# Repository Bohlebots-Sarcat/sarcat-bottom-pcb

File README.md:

# main/sarcat-bottom-pcb

## Sarcat PCB
___
Bohlebots Sarcat bottom circuit board

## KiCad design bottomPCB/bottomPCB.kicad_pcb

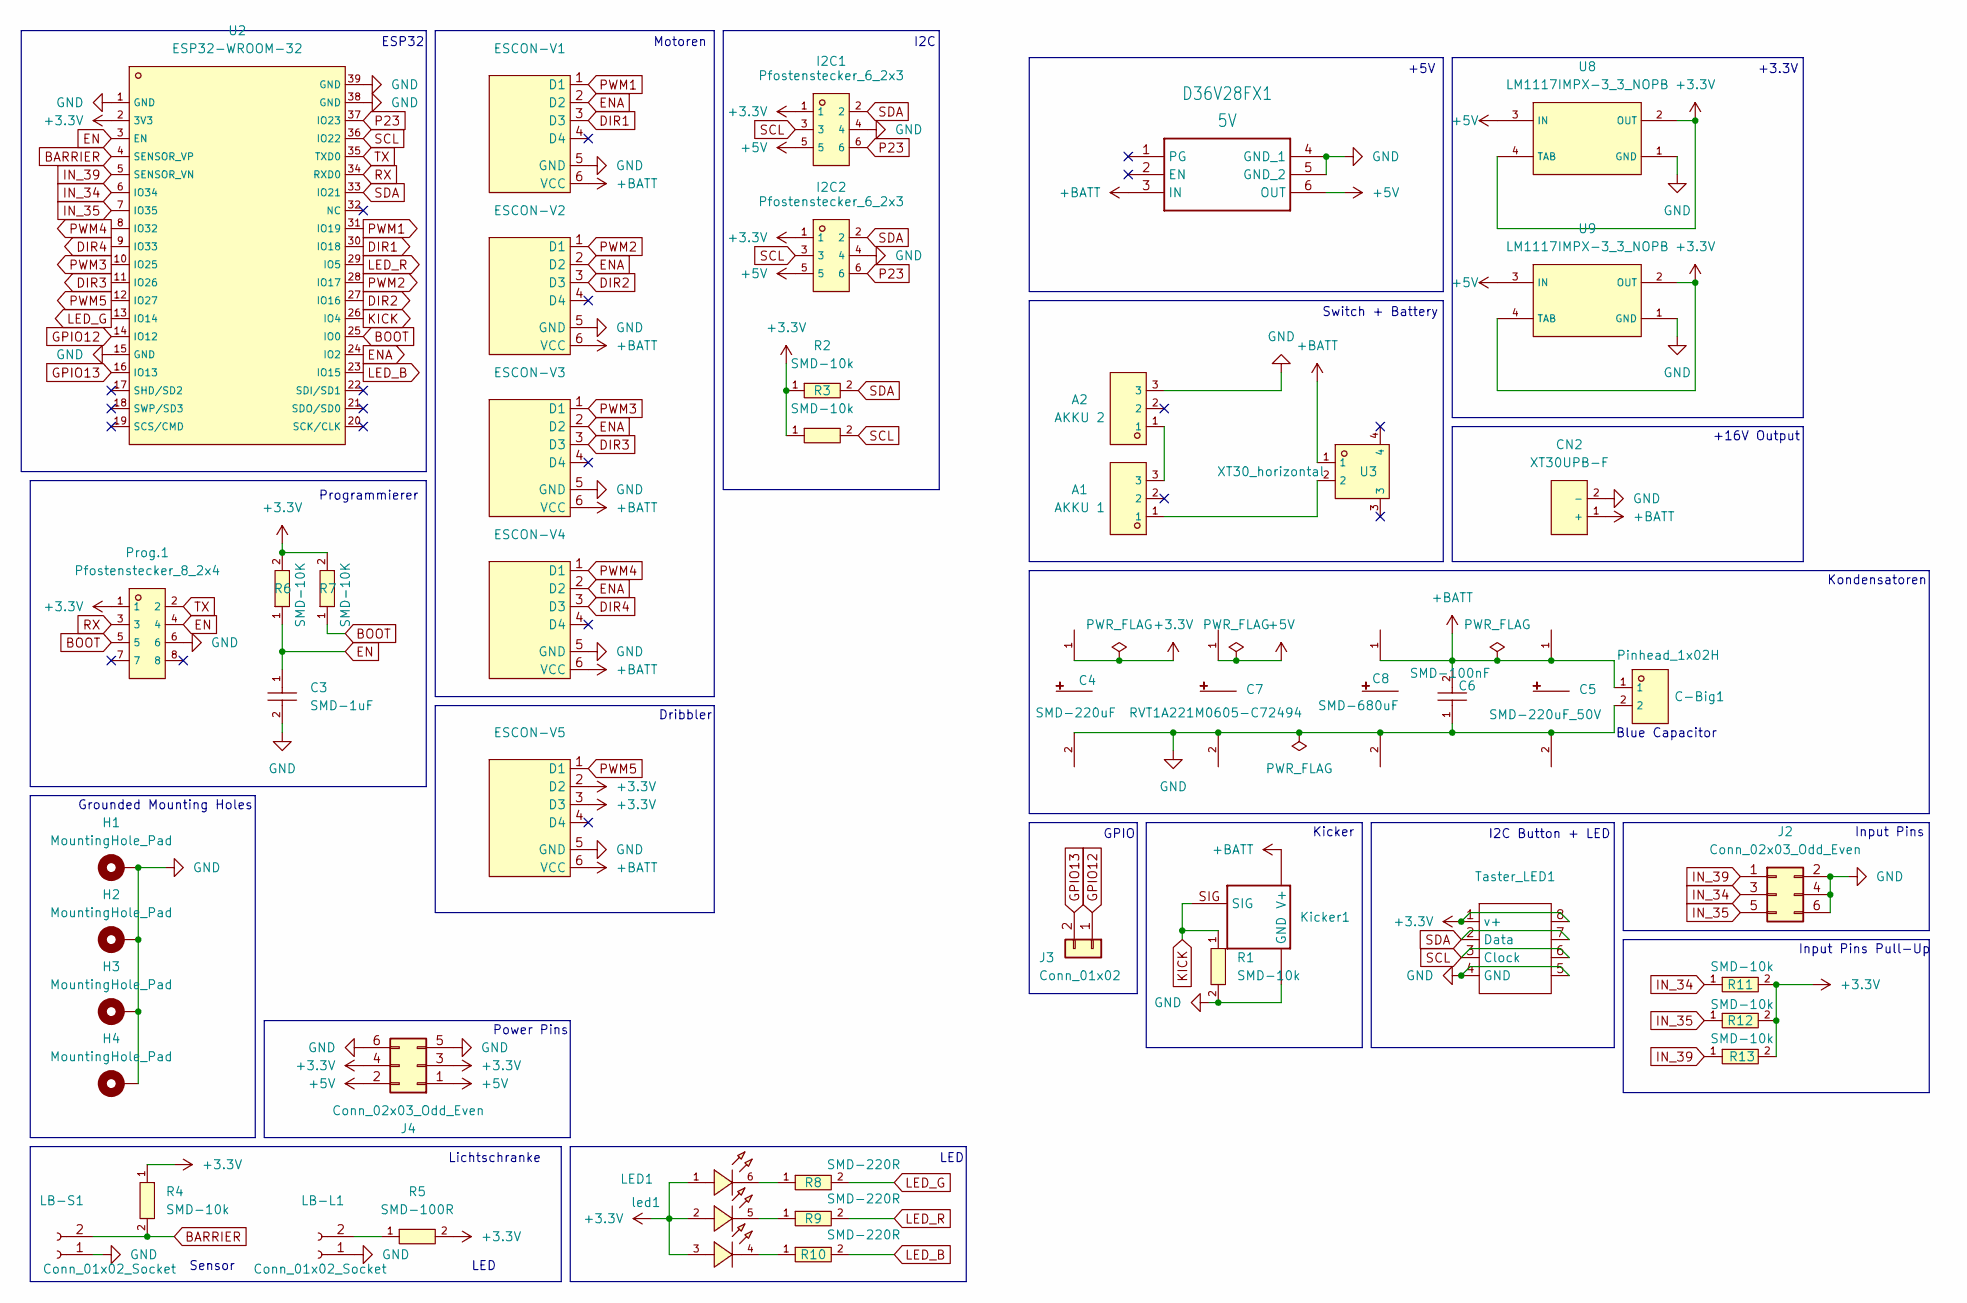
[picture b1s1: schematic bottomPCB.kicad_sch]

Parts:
A1: AKKU 1; CONN-TH_XH-3AW-C722865; LCSC C722865
A2: AKKU 2; CONN-TH_XH-3AW-C722865; LCSC C722865
C3: SMD-1uF; C0603; LCSC C1592
C4: SMD-220uF; CAP-SMD_BD10.0-L10.3-W10.3-LS11.3-FD; LCSC C125977
C5: SMD-220uF_50V; CAP-SMD_BD10.0-L10.3-W10.3-LS11.3-FD; LCSC C125977
C6: SMD-100nF; C0603; LCSC C30926
C7: RVT1A221M0605-C72494; CAP-SMD_BD10.0-L10.3-W10.3-LS11.3-FD; LCSC C125977
C8: SMD-680uF; CAP-SMD_BD10.0-L10.3-W10.3-LS11.3-FD; LCSC C335987
C-Big1: Pinhead_1x02H; HDR-TH_2P-P2.54-H-M-W10.4; LCSC C492410
CN2: XT30UPB-F; CONN-TH_XT30UPB-F; LCSC C108769
D36V28FX1: 5V; D36V28FX
ESCON-V1, ESCON-V2, ESCON-V3, ESCON-V4, ESCON-V5: ESCON-V
H1, H2, H3, H4: MountingHole_Pad; MountingHole_4.3mm_M4_Pad
I2C1, I2C2: Pfostenstecker_6_2x3; HDR-TH_6P-P2.54-V-F-R2-C3-S2.54-4; LCSC C5372863
J2, J4: Conn_02x03_Odd_Even; PinSocket_2x03_P2.54mm_Vertical
J3: Conn_01x02; PinSocket_1x02_P2.54mm_Vertical
Kicker1: KICKER
LB-L1: Conn_01x02_Socket; PinSocket_1x02_P2.54mm_Vertical
LB-S1: Conn_01x02_Socket; PinSocket_1x02_P2.54mm_Vertical
LED1: led1; LED-SMD_6P-L5.0-W5.0-TL_TC5050RGBF08; LCSC C784540
Prog.1: Pfostenstecker_8_2x4; IDC-TH_8P-P2.54-V-R2-C4-S2.54; LCSC C5372864
R1, R2, R3, R4, R11, R12, R13: SMD-10k; R0603; LCSC C25804
R5: SMD-100R; R0603; LCSC C22775
R6, R7: SMD-10K; R0603; LCSC C25804
R8, R9, R10: SMD-220R; R0603; LCSC C217883
Taster_LED1: TASTER_LED
U2: ESP32-WROOM-32; WIFIM-SMD_ESP32-WROOM-32-N4; LCSC C82899
U3: XT30_horizontal; CONN-TH_XT30PW-M; LCSC C431092
U8, U9: LM1117IMPX-3_3_NOPB; SOT-223_L6.5-W3.5-P2.30-LS7.0-BR; LCSC C23984

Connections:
+3.3V: C4.1, ESCON-V5.2 (D2), ESCON-V5.3 (D3), I2C1.1, I2C2.1, J4.3, J4.4, LED1.1 (+), LED1.2 (+), LED1.3 (+), Prog.1.1, R2.1, R3.1, R4.1, R5.2, R6.2, R7.2, R11.2, R12.2, R13.2, Taster_LED1.1 (v+), Taster_LED1.8, U2.2 (3V3), U8.2 (OUT), U8.4 (TAB), U9.2 (OUT), U9.4 (TAB)
+5V: C7.1, D36V28FX1.6 (OUT), I2C1.5, I2C2.5, J4.1, J4.2, U8.3 (IN), U9.3 (IN)
+BATT: C5.1, C6.2, C8.1, C-Big1.1, CN2.1 (+), D36V28FX1.3 (IN), ESCON-V1.6 (VCC), ESCON-V2.6 (VCC), ESCON-V3.6 (VCC), ESCON-V4.6 (VCC), ESCON-V5.6 (VCC), Kicker1.V+1 (V+), Kicker1.V+2 (V+), Kicker1.V+3 (V+), U3.1
BARRIER: LB-S1.2, R4.2, U2.4 (SENSOR_VP)
BOOT: Prog.1.5, R7.1, U2.25 (IO0)
DIR1: ESCON-V1.3 (D3), U2.30 (IO18)
DIR2: ESCON-V2.3 (D3), U2.27 (IO16)
DIR3: ESCON-V3.3 (D3), U2.11 (IO26)
DIR4: ESCON-V4.3 (D3), U2.9 (IO33)
EN: C3.1, Prog.1.4, R6.1, U2.3 (EN)
ENA: ESCON-V1.2 (D2), ESCON-V2.2 (D2), ESCON-V3.2 (D2), ESCON-V4.2 (D2), U2.24 (IO2)
GND: A2.3, C3.2, C4.2, C5.2, C6.1, C7.2, C8.2, C-Big1.2, CN2.2 (-), D36V28FX1.4 (GND_1), D36V28FX1.5 (GND_2), ESCON-V1.5 (GND), ESCON-V2.5 (GND), ESCON-V3.5 (GND), ESCON-V4.5 (GND), ESCON-V5.5 (GND), H1.1, H2.1, H3.1, H4.1, I2C1.4, I2C2.4, J2.2, J2.4, J2.6, J4.5, J4.6, Kicker1.GND1 (GND), Kicker1.GND2 (GND), Kicker1.GND3 (GND), Kicker1.GND4 (GND), Kicker1.GND5 (GND), Kicker1.GND6 (GND), Kicker1.GND7 (GND), Kicker1.GND8 (GND), LB-L1.1, LB-S1.1, Prog.1.6, R1.2, Taster_LED1.4 (GND), Taster_LED1.5, U2.1 (GND), U2.15 (GND), U2.38 (GND), U2.39 (GND), U8.1 (GND), U9.1 (GND)
GPIO12: J3.1, U2.14 (IO12)
GPIO13: J3.2, U2.16 (IO13)
IN_34: J2.3, R11.1, U2.6 (IO34)
IN_35: J2.5, R12.1, U2.7 (IO35)
IN_39: J2.1, R13.1, U2.5 (SENSOR_VN)
KICK: Kicker1.SIG, R1.1, U2.26 (IO4)
LED_B: R10.2, U2.23 (IO15)
LED_G: R8.2, U2.13 (IO14)
LED_R: R9.2, U2.29 (IO5)
unnamed: A1.1, U3.2
unnamed: A1.3, A2.1
unnamed: LB-L1.2, R5.1
unnamed: LED1.4 (-), R10.1
unnamed: LED1.5 (-), R9.1
unnamed: LED1.6 (-), R8.1
P23: I2C1.6, I2C2.6, U2.37 (IO23)
PWM1: ESCON-V1.1 (D1), U2.31 (IO19)
PWM2: ESCON-V2.1 (D1), U2.28 (IO17)
PWM3: ESCON-V3.1 (D1), U2.10 (IO25)
PWM4: ESCON-V4.1 (D1), U2.8 (IO32)
PWM5: ESCON-V5.1 (D1), U2.12 (IO27)
RX: Prog.1.3, U2.34 (RXD0)
SCL: I2C1.3, I2C2.3, R3.2, Taster_LED1.3 (Clock), Taster_LED1.6, U2.36 (IO22)
SDA: I2C1.2, I2C2.2, R2.2, Taster_LED1.2 (Data), Taster_LED1.7, U2.33 (IO21)
TX: Prog.1.2, U2.35 (TXD0)

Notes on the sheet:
Switch + Battery
Grounded Mounting Holes
Dribbler
LED
Motoren
Kondensatoren
+16V Output
I2C Button + LED
I2C
Input Pins
Input Pins Pull-Up
GPIO
Sensor
ESP32
+3.3V
LED
+5V
Kicker
Lichtschranke
Programmierer
Blue Capacitor
Power Pins

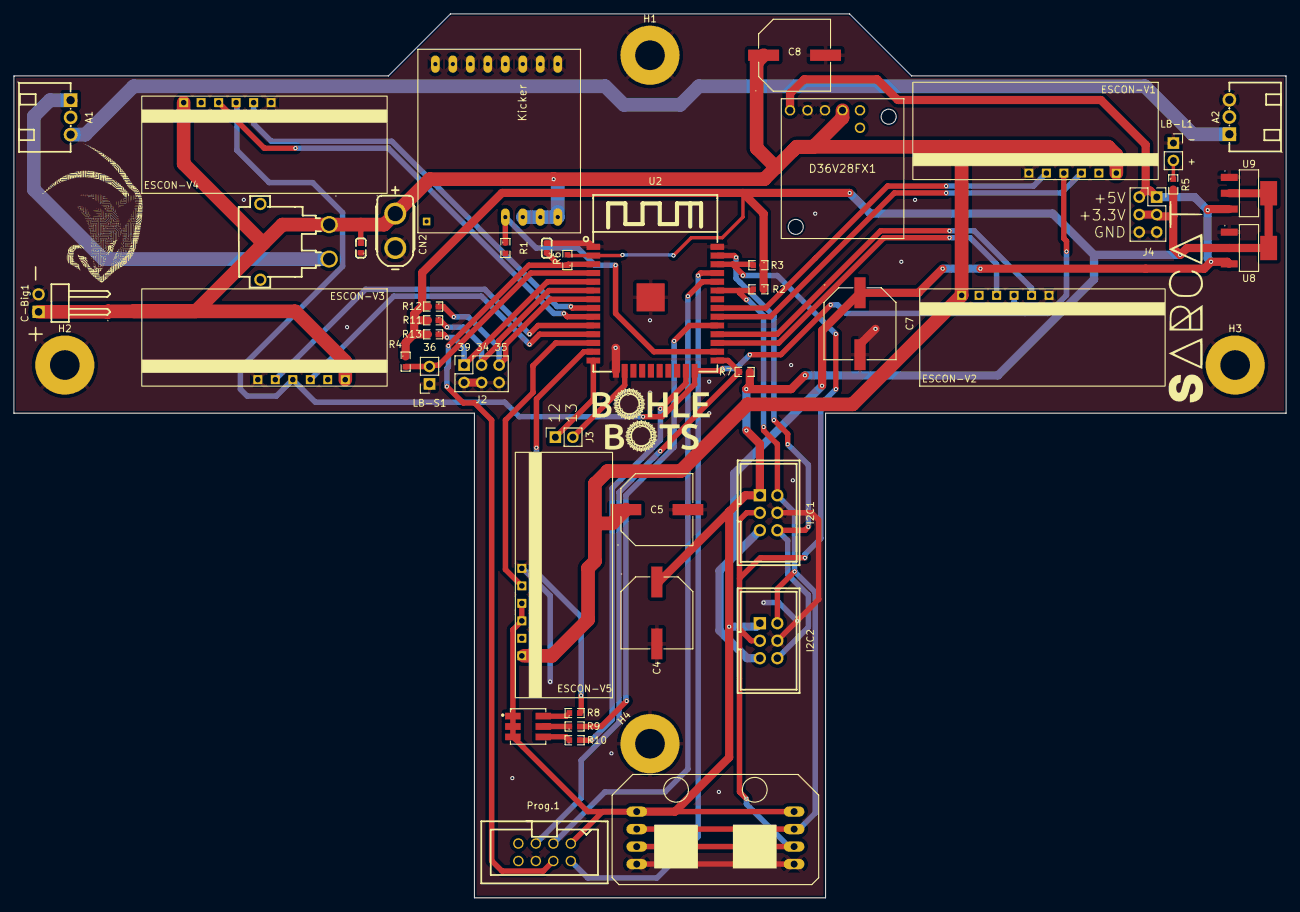
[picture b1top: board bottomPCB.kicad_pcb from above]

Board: 2 copper layers, 184.8 x 128.4 mm, 48 parts (0 on the bottom side), 37 nets.

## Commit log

2024-05-14 add kicad
2024-05-14 changed readme + gitignore
2024-05-14 testfile
2024-05-14 testfile removed
2024-05-14 init done
2024-05-14 added basic parts
2024-05-26 added motor symbol
2024-05-26 added motor + drivers
2024-05-27 added programmer
2024-05-28 added kicker
2024-05-29 simlified to one header pin
2024-06-03 added i2c + kicker resistor
2024-06-03 lichtschranke
2024-06-03 added programmer (boot/EN) Resistors + debounce capacitor
2024-06-03 added power system + capacitators
2024-06-04 added comments
2024-06-04 replaced horizontal header pins with pin socket
2024-06-04 added big blue capacitor
2024-06-04 added dribbler
2024-06-04 improved wiring for motors
2024-06-04 added i2c button interface
2024-06-07 replaced +16V global net with +Batt power symbol
2024-06-07 replaced dribbler escon driver with pins for external driver
2024-06-07 removed unused nets
2024-06-08 migrated global bohlebots lib to project lib
2024-06-08 replaced 2000mA r78 a 5v Regulator with 4000mA D36V26FX 5v Regulator
2024-06-08 added 16V output xt30 connector
2024-06-09 added LED
2024-06-10 added 3 Pullup-Input pins and 2 GPIO pins
2024-06-10 added power pins
2024-06-10 WIP: removed switch
2024-06-14 added ec 20 flat smd conncetor (TE 1-84953-1)
2024-06-14 .gitignore
2024-06-14 connected ec 20 flat connectors to esp32
2024-06-14 Import to PCB editor
2024-06-14 first placement of electronics on pcb
2024-06-14 draft of pcb outline + placement of electronics
2024-06-15 set edge cuts
2024-06-15 use edge cut polygons
2024-06-18 set edge cuts to octagon
2024-06-18 rearranged electronics to fit octagon
2024-06-18 added xt30 horizontal as switch
2024-06-18 replaced smd connectors for ec flat with BohleBots standard
2024-06-18 set standard connectors for motors
2024-06-24 removed useless libs
2024-06-24 added vertical escon driver
2024-06-24 added lib files
2024-06-24 fixed wrong pin rotation in escon-v
2024-06-24 replaced escon drivers with vertical breakout board
2024-06-24 updated pcb
2024-06-24 rearranged for vertical motor drivers
2024-06-24 added rules + changed layout
2024-06-25 set traces
2024-06-25 removed unconnected trace
2024-06-25 removed useless gnd traces
2024-06-25 added silk screen (polarity, pinout)
2024-06-25 centered mounting hole h1
2024-06-25 added logo
2024-06-25 added GND Vias for best possible ground plane
2024-06-25 mend
2024-06-25 V2.0
2024-06-25 moved Connectors to accomodate vertical drivers
2024-06-26 edited footprint for vertical Escon Driver
2024-06-26 moved drivers for motors 3 and 4 to acommodate switch
2024-06-26 edited footprint for vertical Escon Driver, set connector image to Fab Layer
2024-06-26 moved dribbler escon driver to accomodate connector
2024-06-26 made space for kicker
2024-06-26 Updated .gitignore
2024-06-26 removed round tracks config file
2024-06-26 Grounded Mounting Holes
2024-06-26 fixed isolated island issue
2024-06-26 Fixed clippes Sarcat label
2024-06-27 fixed erc errors
2024-06-27 replaced esp32 footprint with new one
2024-07-01 Gerber Files
2024-07-11 Production
